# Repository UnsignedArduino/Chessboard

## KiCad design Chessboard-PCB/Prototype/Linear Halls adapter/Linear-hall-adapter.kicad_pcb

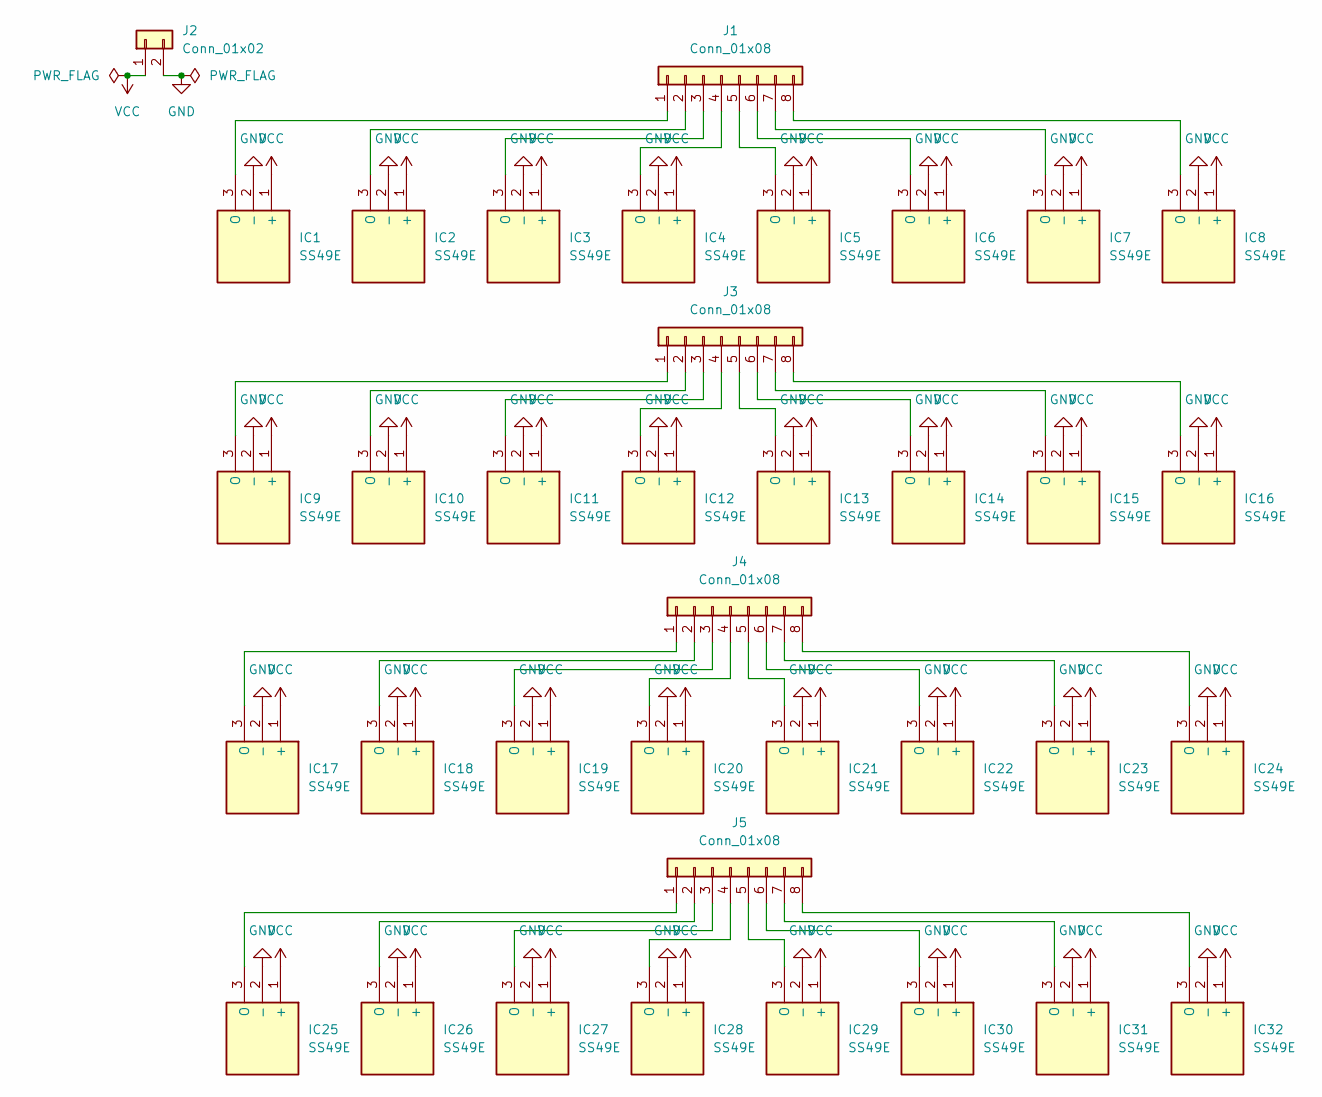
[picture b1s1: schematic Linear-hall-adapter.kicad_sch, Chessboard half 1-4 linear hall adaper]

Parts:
IC1, IC2, IC3, IC4, IC5, IC6, IC7, IC8, IC9, IC10, IC11, IC12, IC13, IC14, IC15, IC16, IC17, IC18, IC19, IC20, IC21, IC22, IC23, IC24, IC25, IC26, IC27, IC28, IC29, IC30, IC31, IC32: SS49E; TO130P160X410X300-3P; Manufacturer_Part_Number SS49E; Mouser Part Number 785-SS49E
J1, J3, J4, J5: Conn_01x08; PinHeader_1x08_P2.54mm_Vertical
J2: Conn_01x02; PinHeader_1x02_P2.54mm_Vertical

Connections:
GND: IC1.2 (-), IC2.2 (-), IC3.2 (-), IC4.2 (-), IC5.2 (-), IC6.2 (-), IC7.2 (-), IC8.2 (-), IC9.2 (-), IC10.2 (-), IC11.2 (-), IC12.2 (-), IC13.2 (-), IC14.2 (-), IC15.2 (-), IC16.2 (-), IC17.2 (-), IC18.2 (-), IC19.2 (-), IC20.2 (-), IC21.2 (-), IC22.2 (-), IC23.2 (-), IC24.2 (-), IC25.2 (-), IC26.2 (-), IC27.2 (-), IC28.2 (-), IC29.2 (-), IC30.2 (-), IC31.2 (-), IC32.2 (-), J2.2
unnamed: IC1.3 (O), J1.1
unnamed: IC2.3 (O), J1.2
unnamed: IC3.3 (O), J1.3
unnamed: IC4.3 (O), J1.4
unnamed: IC5.3 (O), J1.5
unnamed: IC6.3 (O), J1.6
unnamed: IC7.3 (O), J1.7
unnamed: IC8.3 (O), J1.8
unnamed: IC9.3 (O), J3.1
unnamed: IC10.3 (O), J3.2
unnamed: IC11.3 (O), J3.3
unnamed: IC12.3 (O), J3.4
unnamed: IC13.3 (O), J3.5
unnamed: IC14.3 (O), J3.6
unnamed: IC15.3 (O), J3.7
unnamed: IC16.3 (O), J3.8
unnamed: IC17.3 (O), J4.1
unnamed: IC18.3 (O), J4.2
unnamed: IC19.3 (O), J4.3
unnamed: IC20.3 (O), J4.4
unnamed: IC21.3 (O), J4.5
unnamed: IC22.3 (O), J4.6
unnamed: IC23.3 (O), J4.7
unnamed: IC24.3 (O), J4.8
unnamed: IC25.3 (O), J5.1
unnamed: IC26.3 (O), J5.2
unnamed: IC27.3 (O), J5.3
unnamed: IC28.3 (O), J5.4
unnamed: IC29.3 (O), J5.5
unnamed: IC30.3 (O), J5.6
unnamed: IC31.3 (O), J5.7
unnamed: IC32.3 (O), J5.8
VCC: IC1.1 (+), IC2.1 (+), IC3.1 (+), IC4.1 (+), IC5.1 (+), IC6.1 (+), IC7.1 (+), IC8.1 (+), IC9.1 (+), IC10.1 (+), IC11.1 (+), IC12.1 (+), IC13.1 (+), IC14.1 (+), IC15.1 (+), IC16.1 (+), IC17.1 (+), IC18.1 (+), IC19.1 (+), IC20.1 (+), IC21.1 (+), IC22.1 (+), IC23.1 (+), IC24.1 (+), IC25.1 (+), IC26.1 (+), IC27.1 (+), IC28.1 (+), IC29.1 (+), IC30.1 (+), IC31.1 (+), IC32.1 (+), J2.1

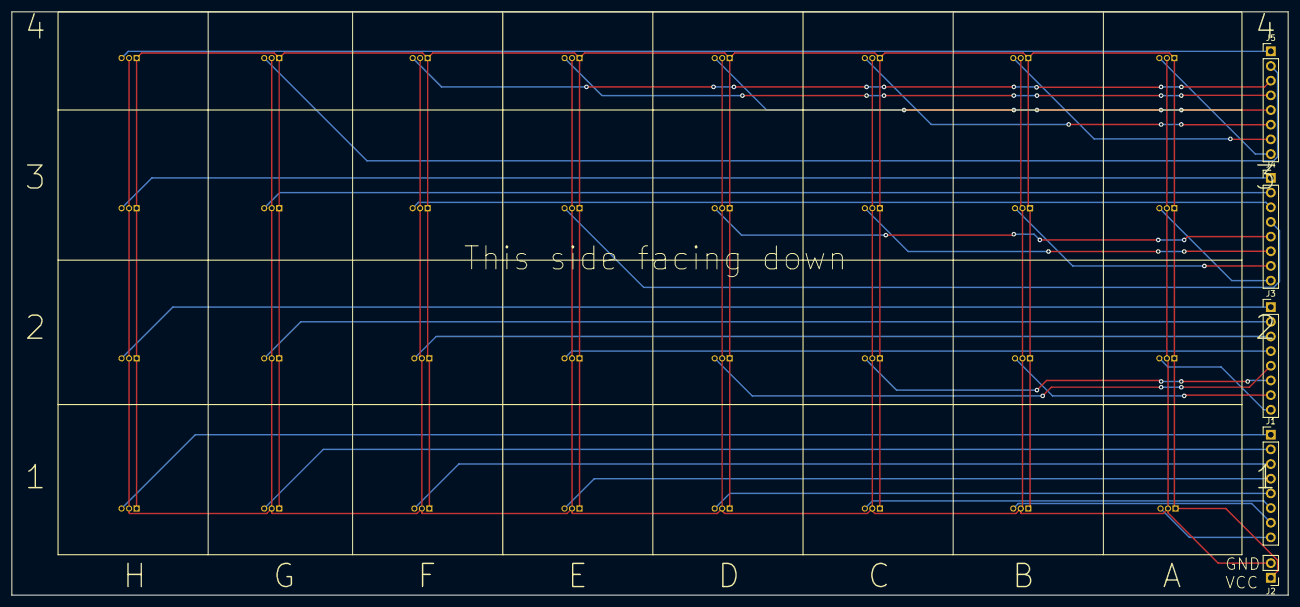
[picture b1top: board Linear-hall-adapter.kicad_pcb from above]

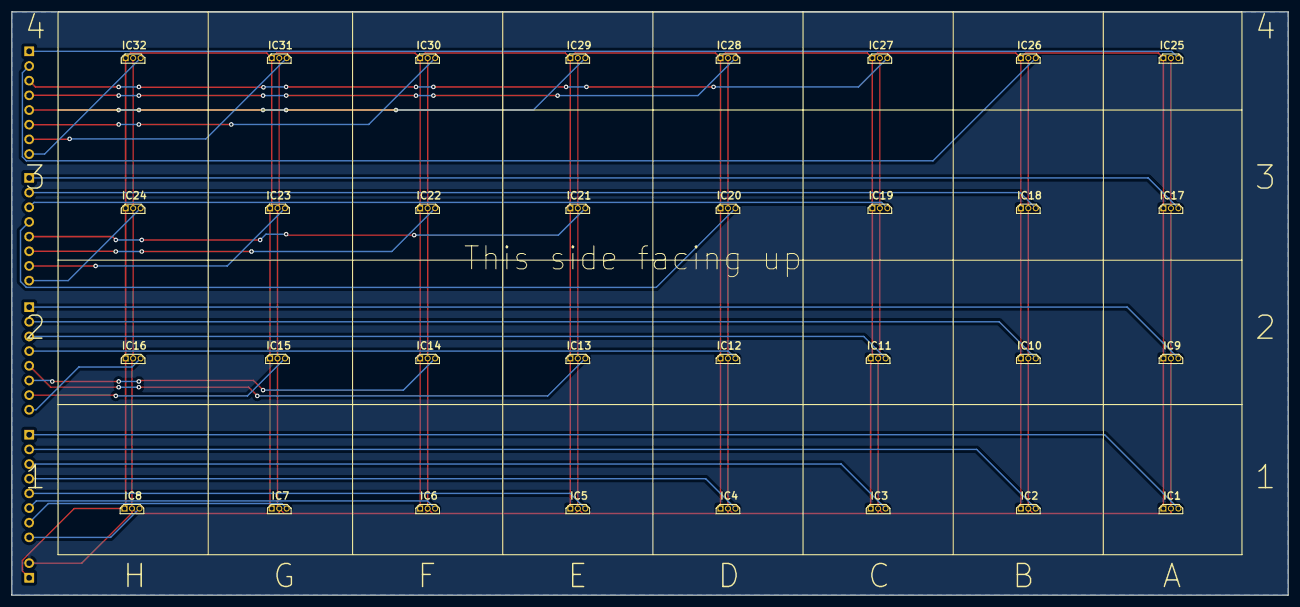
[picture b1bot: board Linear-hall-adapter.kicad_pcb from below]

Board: 2 copper layers, 221.0 x 101.0 mm, 37 parts (32 on the bottom side), 34 nets.

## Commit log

2023-08-09 New Python and PlatformIO projects
2023-08-09 black for Python formatting, pre-commit
2023-08-09 Nano can print board to serial
2023-08-09 Print chessboard state on RPi
2023-08-09 Class for chessboard on Pi
2023-08-09 Interrupt pin, script checks continuously
2023-08-10 Check register for interrupt
2023-08-12 Shift in register test
2023-08-12 Shift out test
2023-08-12 Comments for pins
2023-08-14 Can print changed board
2023-08-14 Nano back as I2C device
2023-08-26 Can rotate and flip board as needed
2023-08-26 Debounce
2023-08-27 Get if reader bits match board
2023-08-27 Rename
2023-08-28 Can follow basic moves
2023-09-01 Can fake board
2023-09-17 Use linear halls and muxs
2023-09-18 Start PCB adaper for linear halls
2023-09-18 Start schematic
2023-09-18 Removed unneeded Kicad files actually
2023-09-18 Move to prototyping
2023-09-18 Start PCB
2023-09-18 Add SS49Es to PCB
2023-09-18 Nice looking footprint for SS49E
2023-09-18 Fix footprints cause I'm bad
2023-09-18 Finish basic PCB
2023-09-19 No PCB
2023-09-19 Undo
2023-09-19 Restart PCB
